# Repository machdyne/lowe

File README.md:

# Löwe FPGA Board

Löwe is an open-source FPGA development board for the Cologne Chip GateMate CCGM1A1.

This repo contains PCB layouts, schematics, pinouts and example gateware.

Find more information on the [Löwe product page](https://machdyne.com/product/lowe-fpga-board/).

## Examples

In order to build the examples, first edit rtl/config.mk and set the paths to the location of your toolchain. You can download the toolchain from [Cologne Chip](https://colognechip.com).

You can build each example with:

```
$ make && make impl
```

You can then use [openFPGALoader](https://github.com/trabucayre/openFPGALoader) to write the gateware to SRAM or flash, using a Raspberry Pi Pico or [Werkzeug](https://github.com/machdyne/werkzeug) (loaded with [pico-dirtyJtag](https://github.com/phdussud/pico-dirtyJtag)) in this example:

```
$ openFPGALoader -c dirtyJtag count_00.cfg.bit
```

## Configuration Mode Selection

The board has 4 DIP switches that select the configuration mode:

| Switches | Mode |
| -------- | ------ |
| 0000 | SPI Active Mode (CPOL=0 CPHA=0) |
| 0001 | SPI Active Mode (CPOL=0 CPHA=1) |
| 0010 | SPI Active Mode (CPOL=1 CPHA=0) |
| 0011 | SPI Active Mode (CPOL=1 CPHA=1) |
| 0100 | SPI Passive Mode (CPOL=0 CPHA=0) |
| 0101 | SPI Passive Mode (CPOL=0 CPHA=1) |
| 0110 | SPI Passive Mode (CPOL=1 CPHA=0) |
| 0111 | SPI Passive Mode (CPOL=1 CPHA=1) |
| 1100 | JTAG |

## MMOD Header

See the [MMOD repo](https://github.com/machdyne/mmod/) for details.

## JTAG Header

The 3.3V JTAG header can be used to program the FPGA SRAM as well as the MMOD flash memory.

```
5 3 1
6 4 2
```

| Pin | Signal |
| --- | ------ |
| 1 | TCK |
| 2 | TDI |
| 3 | TDO |
| 4 | TMS |
| 5 | 5V0[^1] |
| 6 | GND |

[^1]: This pin can be used to power the board with an external regulated 5V power supply, instead of USB power.

## Funding

This project was partially funded through the NGI0 Entrust Fund, a fund established by NLnet with financial support from the European Commission's Next Generation Internet programme.

## License

This project is released under the [CERN-OHL-P](LICENSE.txt) license.

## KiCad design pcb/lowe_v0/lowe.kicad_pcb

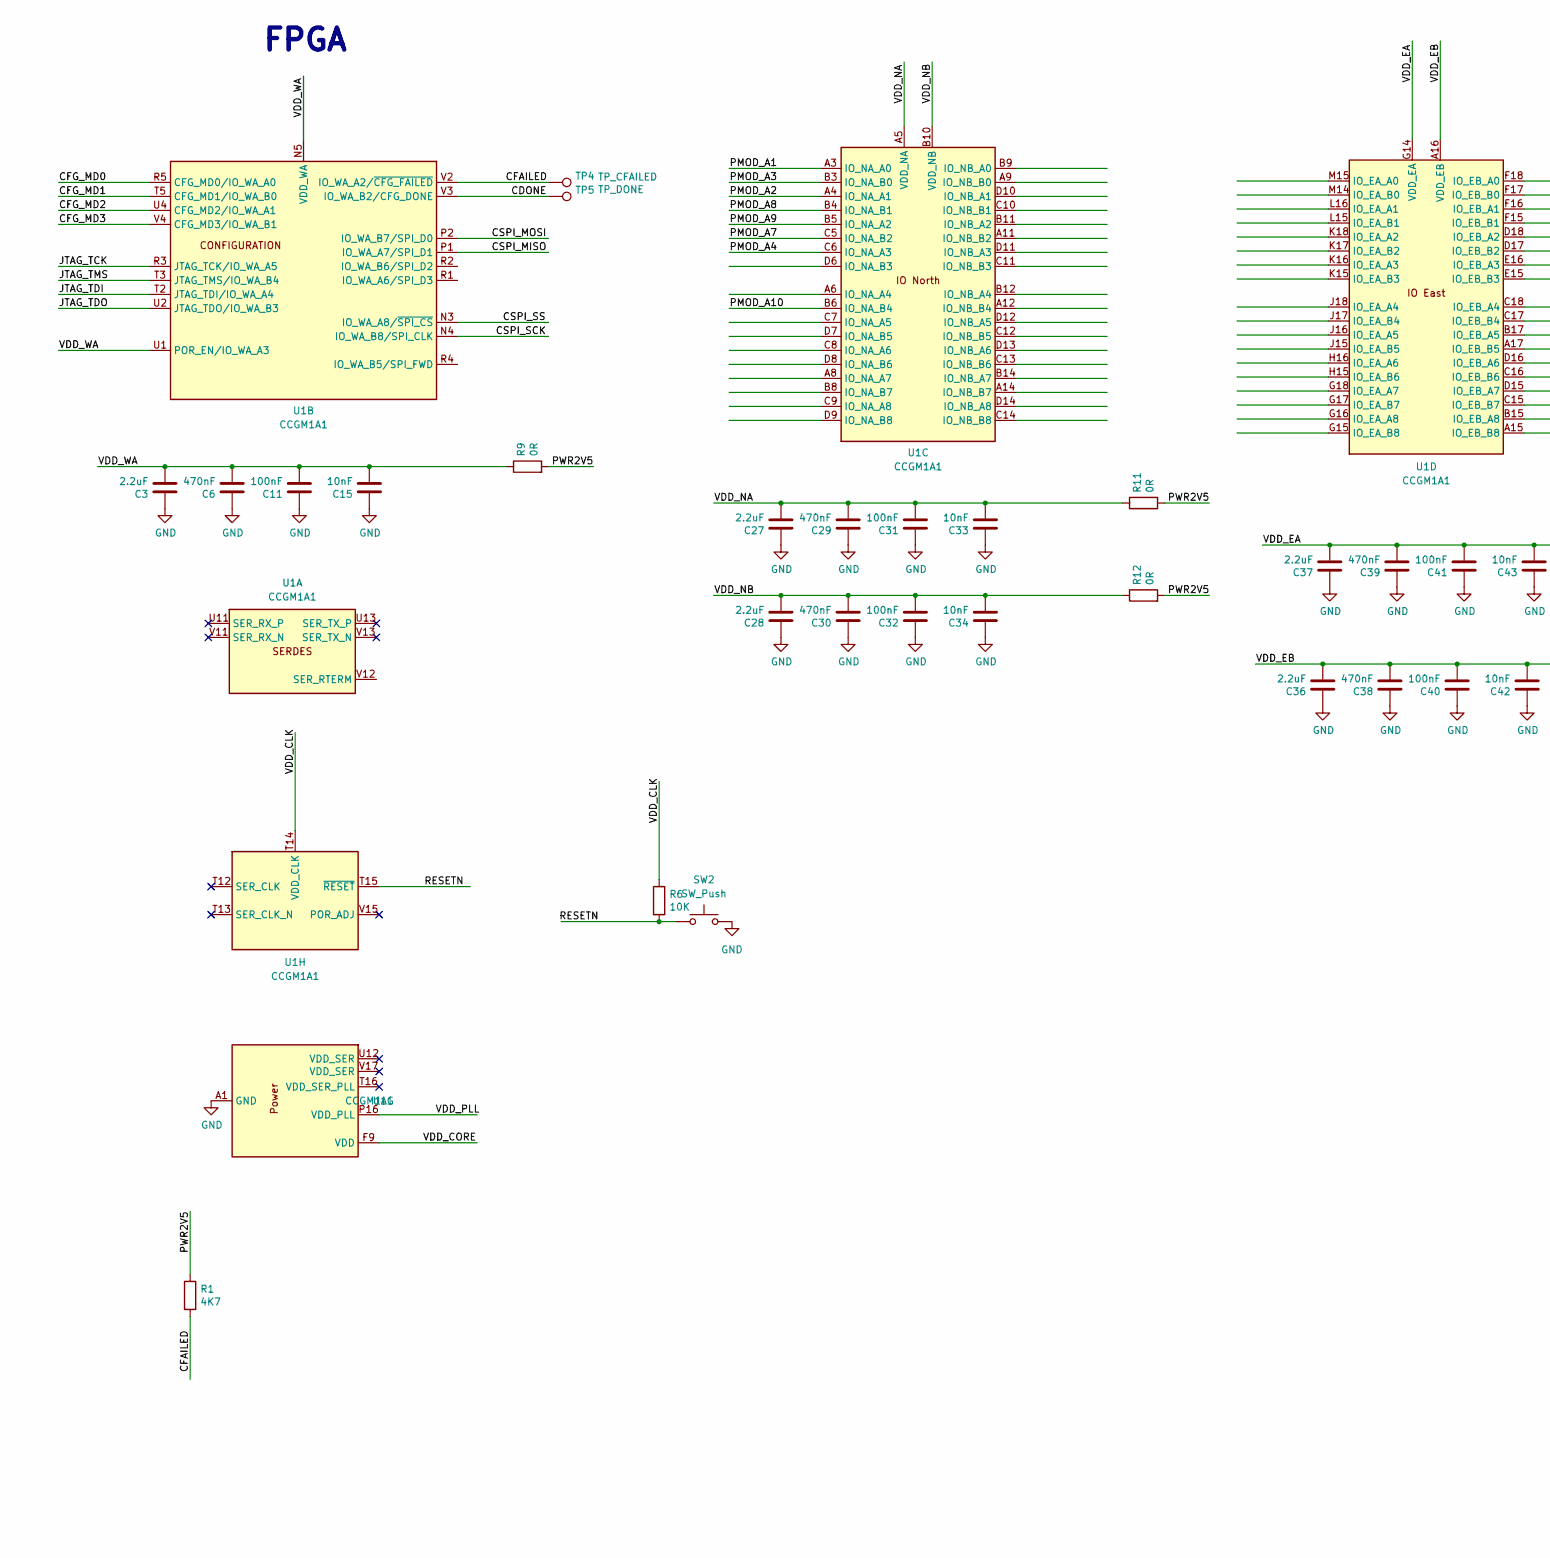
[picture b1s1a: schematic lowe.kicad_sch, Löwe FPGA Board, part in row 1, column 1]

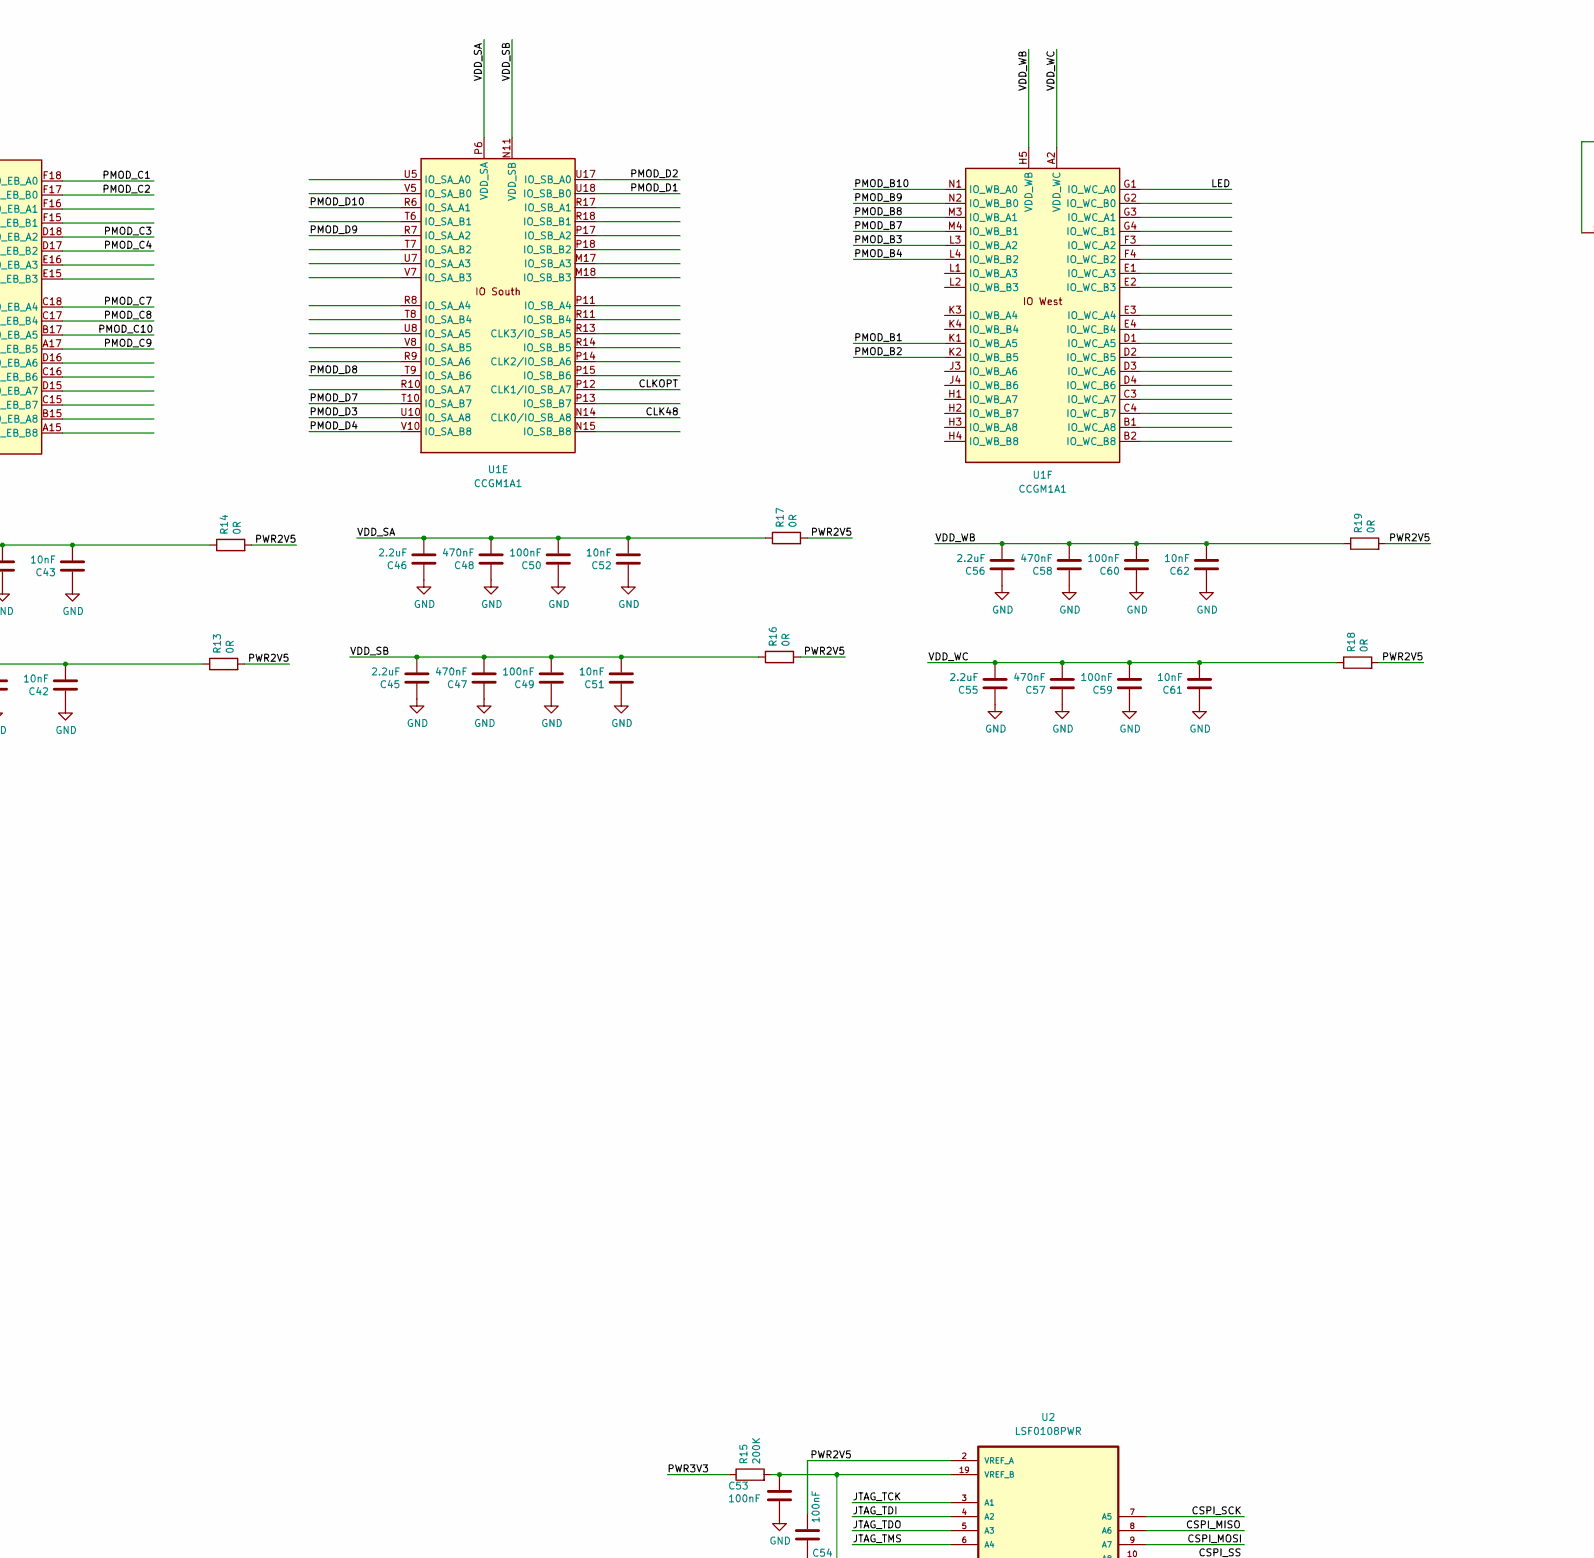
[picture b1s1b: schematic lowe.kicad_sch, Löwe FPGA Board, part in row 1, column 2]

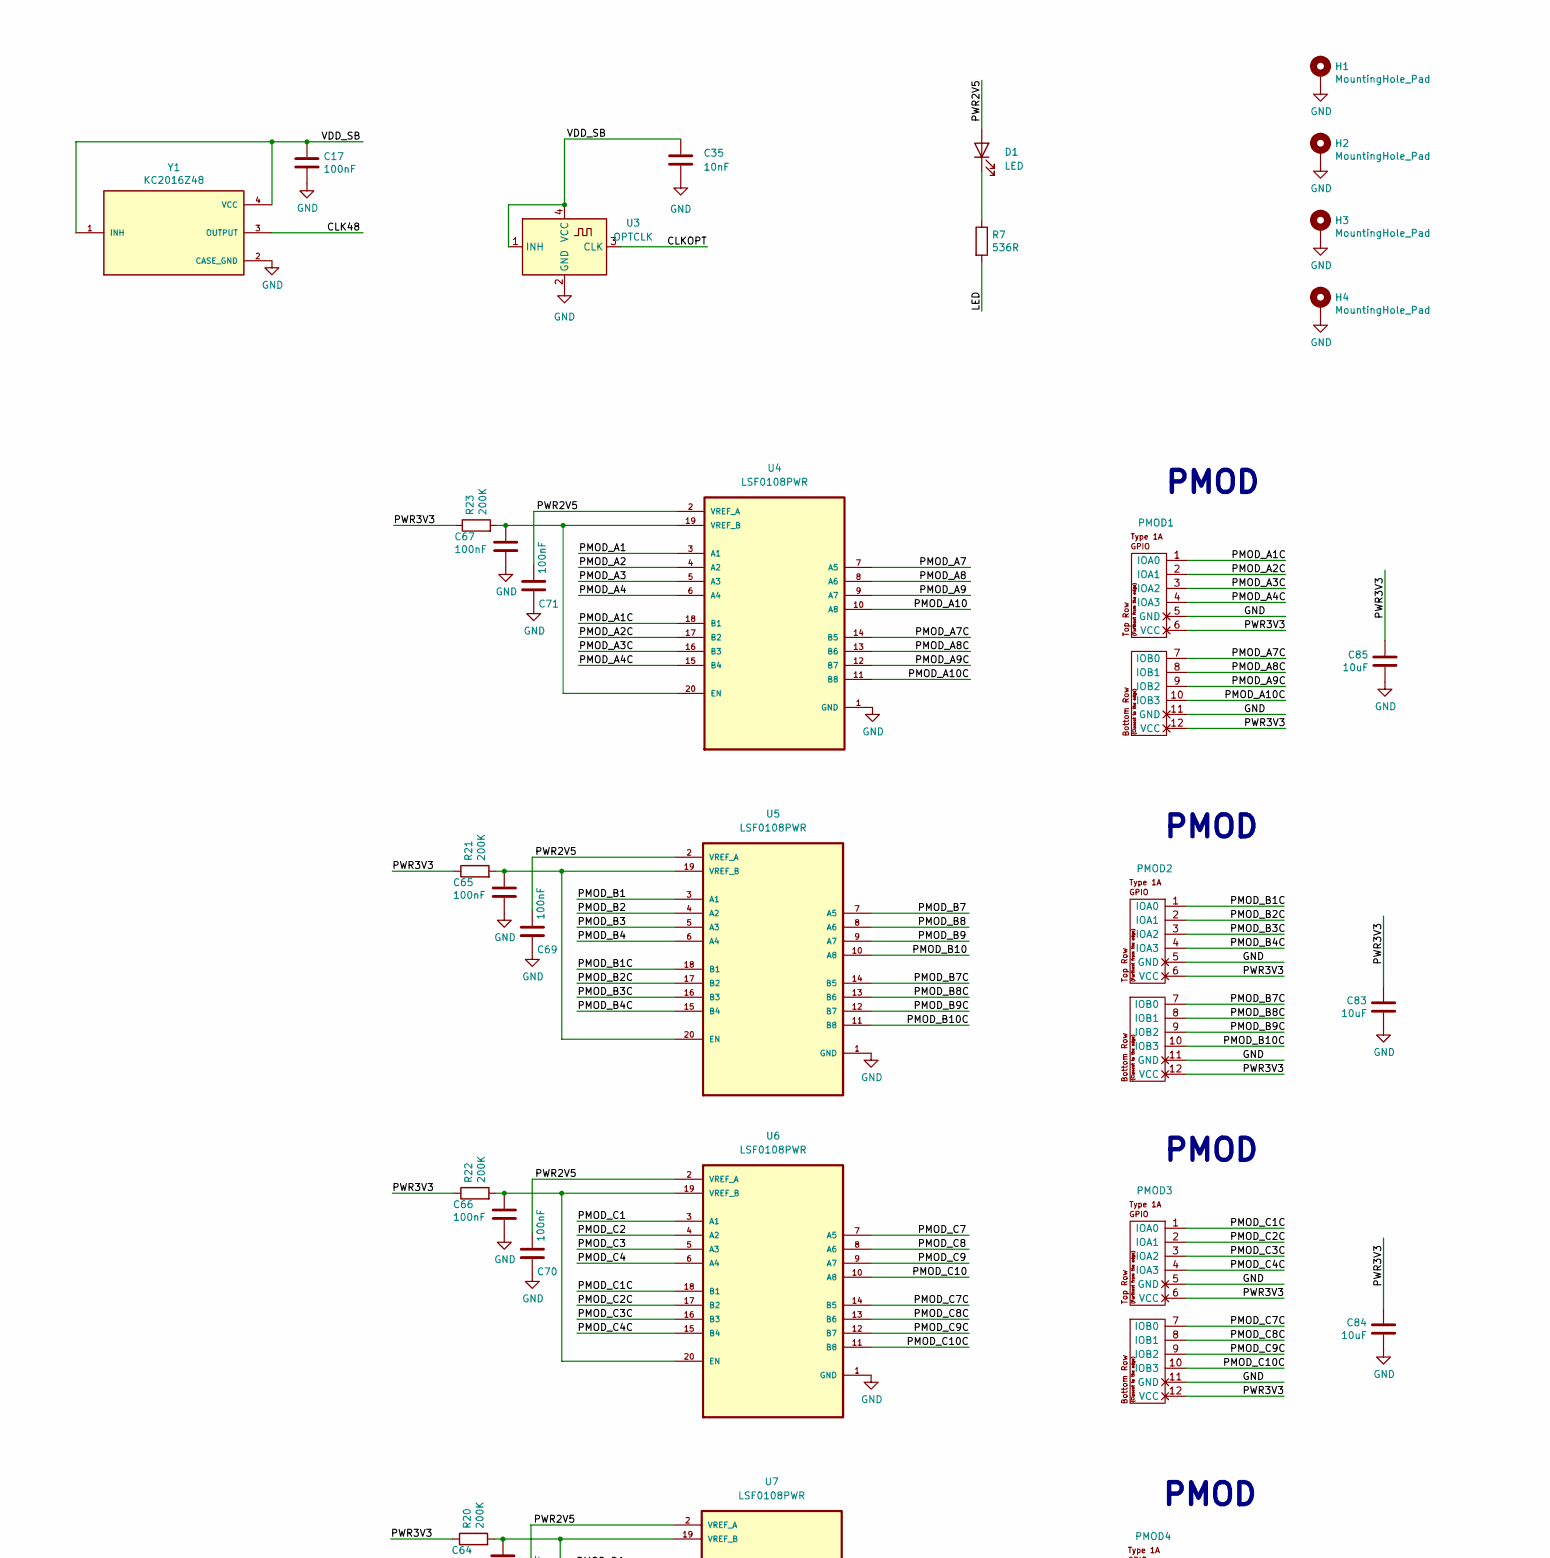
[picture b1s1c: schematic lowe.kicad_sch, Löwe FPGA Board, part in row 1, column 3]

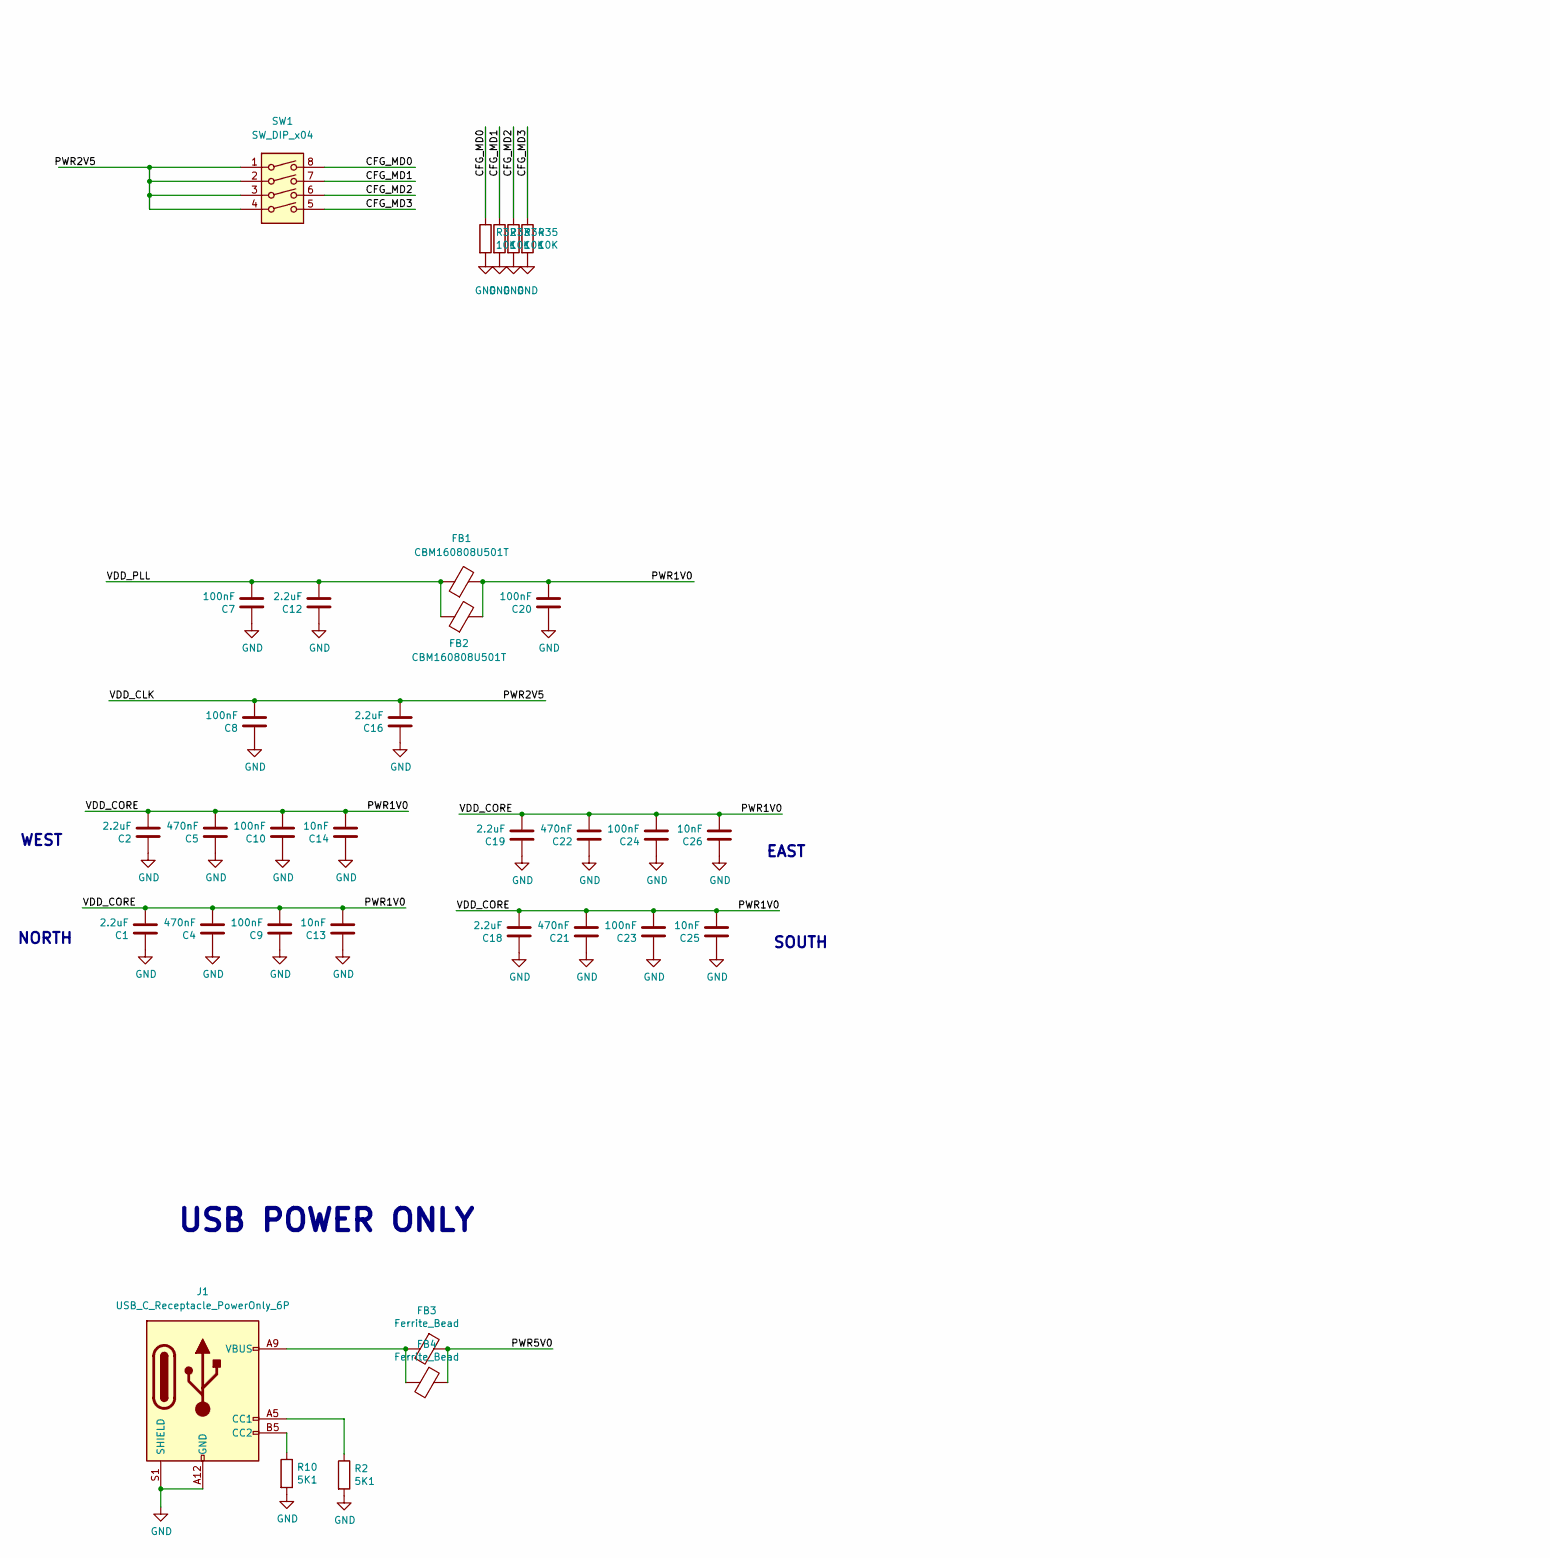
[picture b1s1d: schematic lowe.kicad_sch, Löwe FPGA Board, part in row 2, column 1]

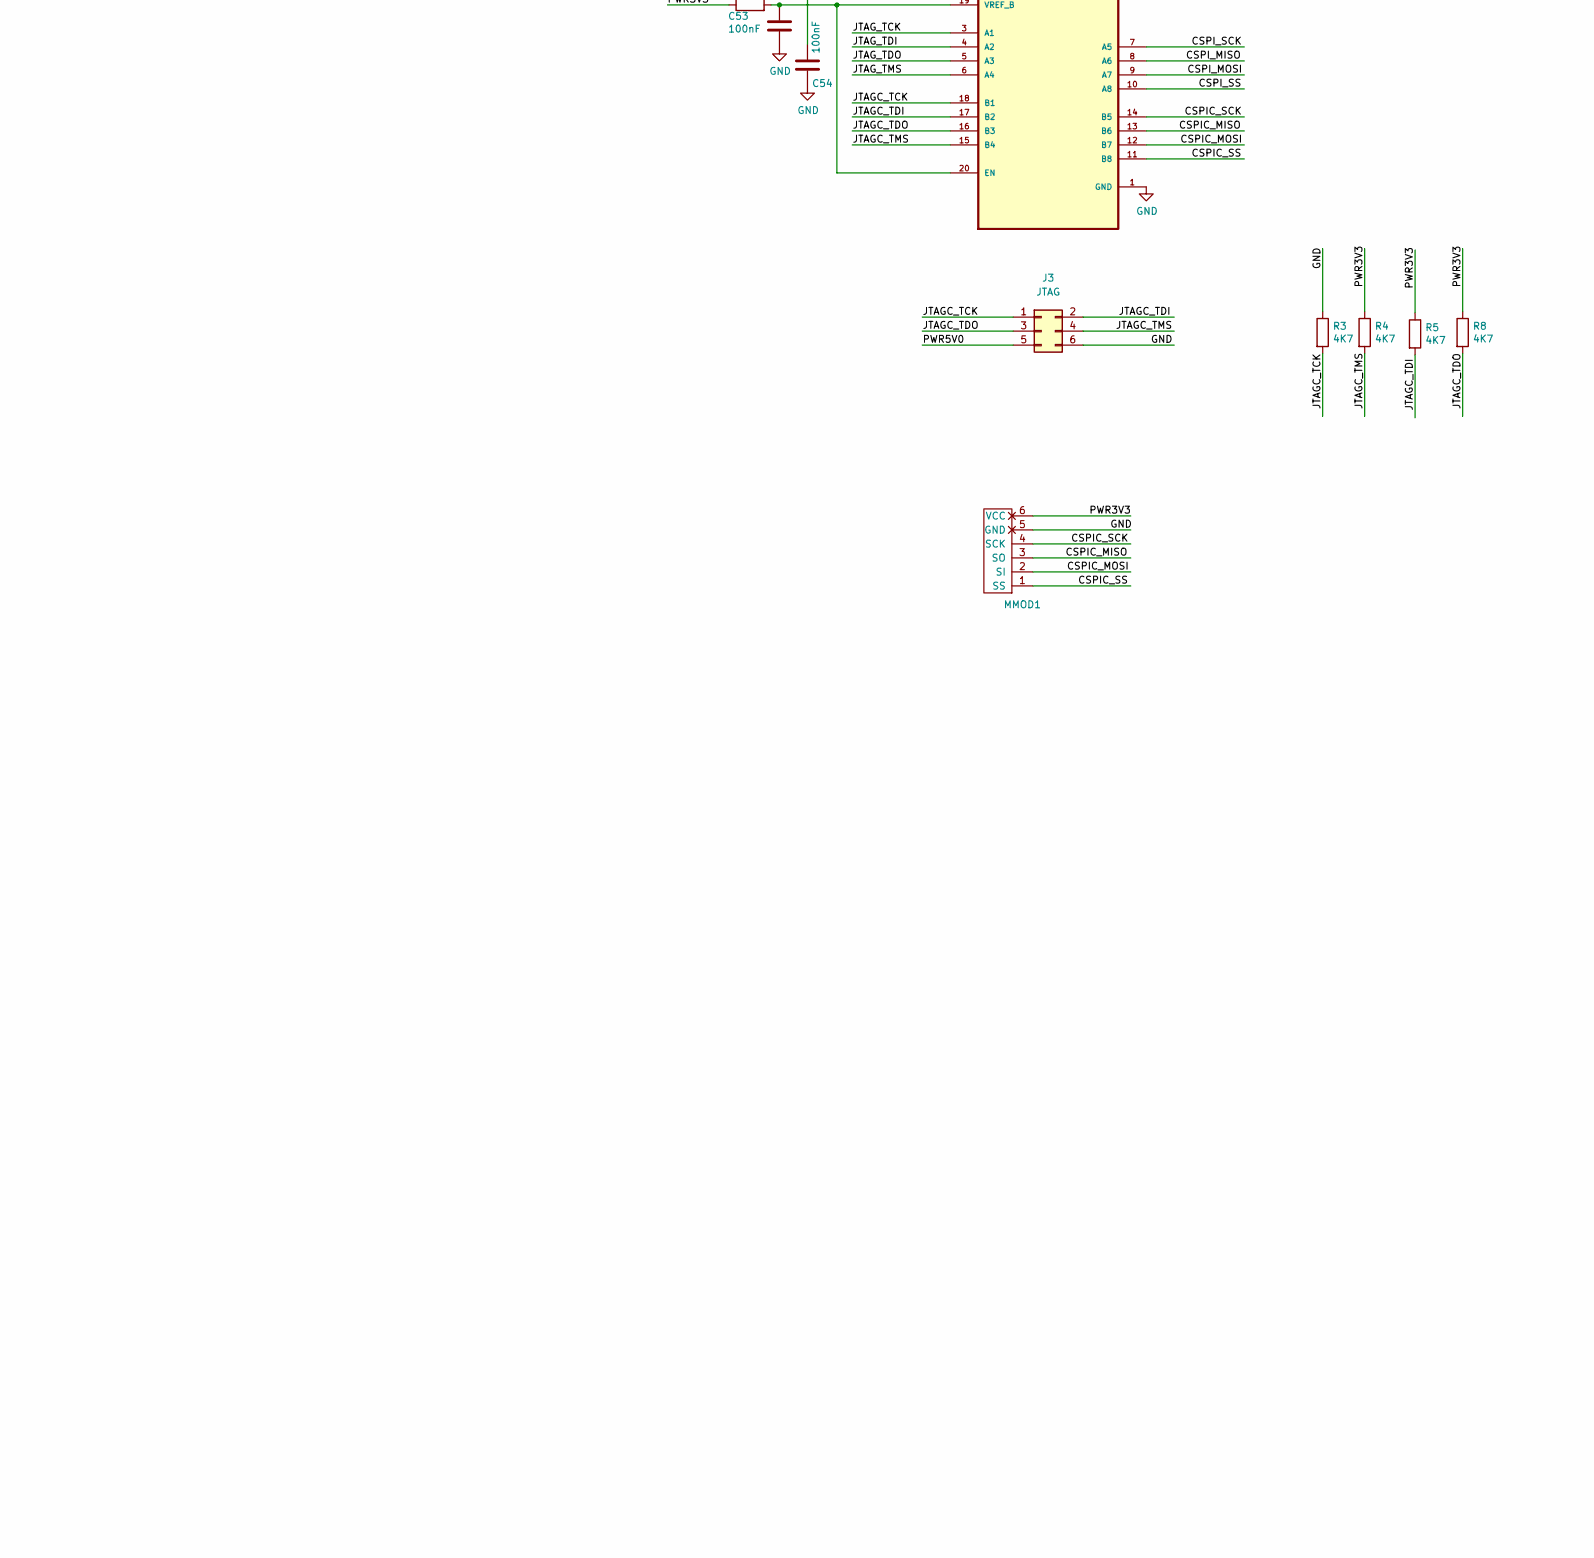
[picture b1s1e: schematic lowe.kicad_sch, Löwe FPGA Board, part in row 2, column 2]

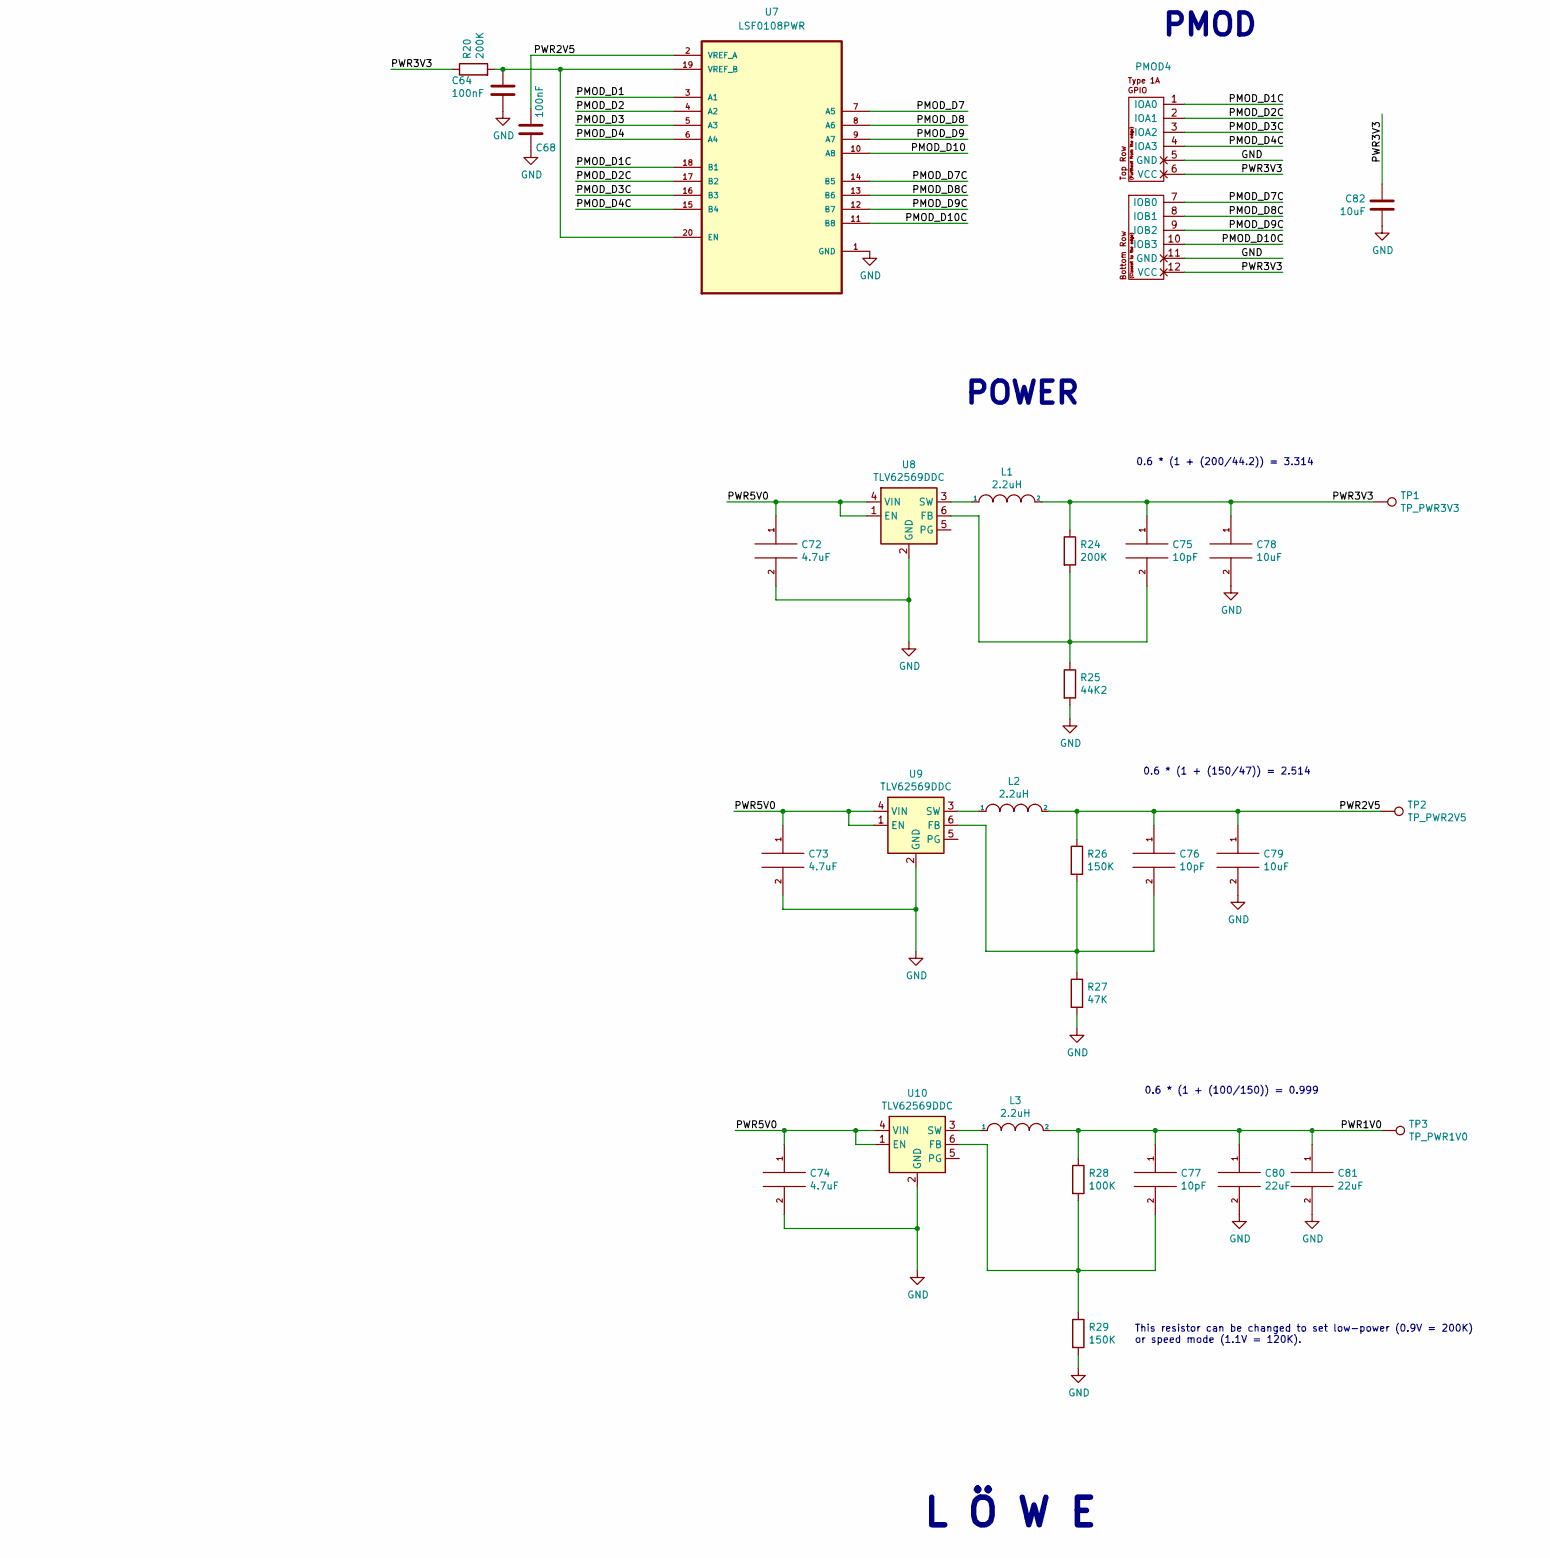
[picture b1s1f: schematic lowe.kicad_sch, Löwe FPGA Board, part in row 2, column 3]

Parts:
C1, C2, C3, C12, C16, C18, C19, C27, C28, C36, C37, C45, C46, C55, C56: 2.2uF; C_0603_1608Metric
C4, C5, C6, C21, C22, C29, C30, C38, C39, C47, C48, C57, C58: 470nF; C_0603_1608Metric
C7, C8, C9, C10, C11, C17, C20, C23, C24, C31, C32, C40, C41, C49, C50, C53, C54, C59, C60, C64, C65, C66, C67, C68, C69, C70, C71: 100nF; C_0603_1608Metric
C13, C14, C15, C25, C26, C33, C34, C35, C42, C43, C51, C52, C61, C62: 10nF; C_0603_1608Metric
C72, C73, C74: 4.7uF; C_0603_1608Metric
C75, C76, C77: 10pF; C_0603_1608Metric
C78, C79, C82, C83, C84, C85: 10uF; C_0603_1608Metric
C80, C81: 22uF; C_0603_1608Metric
D1: LED; LED_0603_1608Metric
FB1, FB2: CBM160808U501T; R_0603_1608Metric
FB3, FB4: Ferrite_Bead; R_0603_1608Metric
H1, H2, H3, H4: MountingHole_Pad; MountingHole_3.2mm_M3_Pad
J1: USB_C_Receptacle_PowerOnly_6P; GCT_USB4125-GF-A_REVA_BIGPADS
J3: JTAG; PinHeader_2x03_P2.54mm_Vertical
L1, L2, L3: 2.2uH; L_Taiyo-Yuden_MD-4040
MMOD1: PMOD-Device-x1-Type-2-SPI; MMOD_Host_Socket
PMOD1, PMOD2, PMOD3, PMOD4: PMOD-Device-x2-Type-1A-GPIO; PMOD_2x06_HOST
R1, R3, R4, R5, R8: 4K7; R_0603_1608Metric
R2, R10: 5K1; R_0603_1608Metric
R6, R32, R33, R34, R35: 10K; R_0603_1608Metric
R7: 536R; R_0603_1608Metric
R9, R11, R12, R13, R14, R16, R17, R18, R19: 0R; LD-NETTIE-0603
R15, R20, R21, R22, R23, R24: 200K; R_0603_1608Metric
R25: 44K2; R_0603_1608Metric
R26, R29: 150K; R_0603_1608Metric
R27: 47K; R_0603_1608Metric
R28: 100K; R_0603_1608Metric
SW1: SW_DIP_x04; SW_DIP_SPSTx04_Slide_6.7x11.72mm_W7.62mm_P2.54mm_LowProfile
SW2: SW_Push; Button_2P_3x4mm
TP1: TP_PWR3V3; TestPoint_THTPad_D1.0mm_Drill0.5mm
TP2: TP_PWR2V5; TestPoint_THTPad_D1.0mm_Drill0.5mm
TP3: TP_PWR1V0; TestPoint_THTPad_D1.0mm_Drill0.5mm
TP4: TP_CFAILED; TestPoint_Pad_1.0x1.0mm
TP5: TP_DONE; TestPoint_Pad_1.0x1.0mm
U1: CCGM1A1; BGA-324_15.0x15.0mm_Layout18x18_P0.8mm_Ball0.5mm_Pad0.4mm_N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
U2, U4, U5, U6, U7: LSF0108PWR; TSSOP-20_4.4x6.5mm_P0.65mm
U3: OPTCLK; Oscillator_SMD_Kyocera_KC2520Z-4Pin_2.5x2.0mm
U8, U9, U10: TLV62569DDC; SOT-23-6
Y1: KC2016Z48; OSC_KC2016Z13.5600C1KX00; PARTREV November 2020

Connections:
/CDONE: TP5.1, U1.V3 (IO_WA_B2/CFG_DONE)
/CFAILED: R1.2, TP4.1, U1.V2 (IO_WA_A2/~CFG_FAILED)
/CFG_MD0: R32.1, SW1.8, U1.R5 (CFG_MD0/IO_WA_A0)
/CFG_MD1: R33.1, SW1.7, U1.T5 (CFG_MD1/IO_WA_B0)
/CFG_MD2: R34.1, SW1.6, U1.U4 (CFG_MD2/IO_WA_A1)
/CFG_MD3: R35.1, SW1.5, U1.V4 (CFG_MD3/IO_WA_B1)
/CLK48: U1.N14 (CLK0/IO_SB_A8), Y1.3 (OUTPUT)
/CLKOPT: U1.P12 (CLK1/IO_SB_A7), U3.3 (CLK)
/CSPIC_MISO: MMOD1.3 (SO), U2.13 (B6)
/CSPIC_MOSI: MMOD1.2 (SI), U2.12 (B7)
/CSPIC_SCK: MMOD1.4 (SCK), U2.14 (B5)
/CSPIC_SS: MMOD1.1 (SS), U2.11 (B8)
/CSPI_MISO: U1.P1 (IO_WA_A7/SPI_D1), U2.8 (A6)
/CSPI_MOSI: U1.P2 (IO_WA_B7/SPI_D0), U2.9 (A7)
/CSPI_SCK: U1.N4 (IO_WA_B8/SPI_CLK), U2.7 (A5)
/CSPI_SS: U1.N3 (IO_WA_A8/~SPI_CS), U2.10 (A8)
/JTAGC_TCK: J3.1, R3.2, U2.18 (B1)
/JTAGC_TDI: J3.2, R5.2, U2.17 (B2)
/JTAGC_TDO: J3.3, R8.2, U2.16 (B3)
/JTAGC_TMS: J3.4, R4.2, U2.15 (B4)
/JTAG_TCK: U1.R3 (JTAG_TCK/IO_WA_A5), U2.3 (A1)
/JTAG_TDI: U1.T2 (JTAG_TDI/IO_WA_A4), U2.4 (A2)
/JTAG_TDO: U1.U2 (JTAG_TDO/IO_WA_B3), U2.5 (A3)
/JTAG_TMS: U1.T3 (JTAG_TMS/IO_WA_B4), U2.6 (A4)
/LED: R7.2, U1.G1 (IO_WC_A0)
/PMOD_A1: U1.A3 (IO_NA_A0), U4.3 (A1)
/PMOD_A1C: PMOD1.1 (IOA0), U4.18 (B1)
/PMOD_A2: U1.A4 (IO_NA_A1), U4.4 (A2)
/PMOD_A2C: PMOD1.2 (IOA1), U4.17 (B2)
/PMOD_A3: U1.B3 (IO_NA_B0), U4.5 (A3)
/PMOD_A3C: PMOD1.3 (IOA2), U4.16 (B3)
/PMOD_A4: U1.C6 (IO_NA_A3), U4.6 (A4)
/PMOD_A4C: PMOD1.4 (IOA3), U4.15 (B4)
/PMOD_A7: U1.C5 (IO_NA_B2), U4.7 (A5)
/PMOD_A7C: PMOD1.7 (IOB0), U4.14 (B5)
/PMOD_A8: U1.B4 (IO_NA_B1), U4.8 (A6)
/PMOD_A8C: PMOD1.8 (IOB1), U4.13 (B6)
/PMOD_A9: U1.B5 (IO_NA_A2), U4.9 (A7)
/PMOD_A9C: PMOD1.9 (IOB2), U4.12 (B7)
/PMOD_A10: U1.B6 (IO_NA_B4), U4.10 (A8)
/PMOD_A10C: PMOD1.10 (IOB3), U4.11 (B8)
/PMOD_B1: U1.K1 (IO_WB_A5), U5.3 (A1)
/PMOD_B1C: PMOD2.1 (IOA0), U5.18 (B1)
/PMOD_B2: U1.K2 (IO_WB_B5), U5.4 (A2)
/PMOD_B2C: PMOD2.2 (IOA1), U5.17 (B2)
/PMOD_B3: U1.L3 (IO_WB_A2), U5.5 (A3)
/PMOD_B3C: PMOD2.3 (IOA2), U5.16 (B3)
/PMOD_B4: U1.L4 (IO_WB_B2), U5.6 (A4)
/PMOD_B4C: PMOD2.4 (IOA3), U5.15 (B4)
/PMOD_B7: U1.M4 (IO_WB_B1), U5.7 (A5)
/PMOD_B7C: PMOD2.7 (IOB0), U5.14 (B5)
/PMOD_B8: U1.M3 (IO_WB_A1), U5.8 (A6)
/PMOD_B8C: PMOD2.8 (IOB1), U5.13 (B6)
/PMOD_B9: U1.N2 (IO_WB_B0), U5.9 (A7)
/PMOD_B9C: PMOD2.9 (IOB2), U5.12 (B7)
/PMOD_B10: U1.N1 (IO_WB_A0), U5.10 (A8)
/PMOD_B10C: PMOD2.10 (IOB3), U5.11 (B8)
/PMOD_C1: U1.F18 (IO_EB_A0), U6.3 (A1)
/PMOD_C1C: PMOD3.1 (IOA0), U6.18 (B1)
/PMOD_C2: U1.F17 (IO_EB_B0), U6.4 (A2)
/PMOD_C2C: PMOD3.2 (IOA1), U6.17 (B2)
/PMOD_C3: U1.D18 (IO_EB_A2), U6.5 (A3)
/PMOD_C3C: PMOD3.3 (IOA2), U6.16 (B3)
/PMOD_C4: U1.D17 (IO_EB_B2), U6.6 (A4)
/PMOD_C4C: PMOD3.4 (IOA3), U6.15 (B4)
/PMOD_C7: U1.C18 (IO_EB_A4), U6.7 (A5)
/PMOD_C7C: PMOD3.7 (IOB0), U6.14 (B5)
/PMOD_C8: U1.C17 (IO_EB_B4), U6.8 (A6)
/PMOD_C8C: PMOD3.8 (IOB1), U6.13 (B6)
/PMOD_C9: U1.A17 (IO_EB_B5), U6.9 (A7)
/PMOD_C9C: PMOD3.9 (IOB2), U6.12 (B7)
/PMOD_C10: U1.B17 (IO_EB_A5), U6.10 (A8)
/PMOD_C10C: PMOD3.10 (IOB3), U6.11 (B8)
/PMOD_D1: U1.U18 (IO_SB_B0), U7.3 (A1)
/PMOD_D1C: PMOD4.1 (IOA0), U7.18 (B1)
/PMOD_D2: U1.U17 (IO_SB_A0), U7.4 (A2)
/PMOD_D2C: PMOD4.2 (IOA1), U7.17 (B2)
/PMOD_D3: U1.U10 (IO_SA_A8), U7.5 (A3)
/PMOD_D3C: PMOD4.3 (IOA2), U7.16 (B3)
/PMOD_D4: U1.V10 (IO_SA_B8), U7.6 (A4)
/PMOD_D4C: PMOD4.4 (IOA3), U7.15 (B4)
/PMOD_D7: U1.T10 (IO_SA_B7), U7.7 (A5)
/PMOD_D7C: PMOD4.7 (IOB0), U7.14 (B5)
/PMOD_D8: U1.T9 (IO_SA_B6), U7.8 (A6)
/PMOD_D8C: PMOD4.8 (IOB1), U7.13 (B6)
/PMOD_D9: U1.R7 (IO_SA_A2), U7.9 (A7)
/PMOD_D9C: PMOD4.9 (IOB2), U7.12 (B7)
/PMOD_D10: U1.R6 (IO_SA_A1), U7.10 (A8)
/PMOD_D10C: PMOD4.10 (IOB3), U7.11 (B8)
/PWR1V0: C1.2, C2.2, C4.2, C5.2, C9.2, C10.2, C13.2, C14.2, C18.2, C19.2, C20.2, C21.2, C22.2, C23.2, C24.2, C25.2, C26.2, C77.1, C80.1, C81.1, FB1.2, FB2.2, L3.2, R28.1, TP3.1, U1.F9 (VDD), U1.G6 (VDD), U1.G8 (VDD), U1.G10 (VDD), U1.G12 (VDD), U1.H7 (VDD), U1.H9 (VDD), U1.H11 (VDD), U1.H13 (VDD), U1.J6 (VDD), U1.J8 (VDD), U1.J10 (VDD), U1.J12 (VDD), U1.K7 (VDD), U1.K9 (VDD), U1.K11 (VDD), U1.K13 (VDD), U1.L6 (VDD), U1.L8 (VDD), U1.L10 (VDD), U1.L12 (VDD), U1.M7 (VDD), U1.M9 (VDD), U1.M11 (VDD), U1.M13 (VDD), U1.N6 (VDD), U1.N8 (VDD), U1.N10 (VDD)
/PWR2V5: C8.2, C16.2, C54.1, C68.1, C69.1, C70.1, C71.1, C76.1, C79.1, D1.2 (A), L2.2, R1.1, R6.1, R9.2, R11.2, R12.2, R13.2, R14.2, R16.2, R17.2, R18.2, R19.2, R26.1, SW1.1, SW1.2, SW1.3, SW1.4, TP2.1, U1.T14 (VDD_CLK), U2.2 (VREF_A), U4.2 (VREF_A), U5.2 (VREF_A), U6.2 (VREF_A), U7.2 (VREF_A)
/PWR3V3: C75.1, C78.1, C82.1, C83.1, C84.1, C85.1, L1.2, MMOD1.6 (VCC), PMOD1.6 (VCC), PMOD1.12 (VCC), PMOD2.6 (VCC), PMOD2.12 (VCC), PMOD3.6 (VCC), PMOD3.12 (VCC), PMOD4.6 (VCC), PMOD4.12 (VCC), R4.1, R5.1, R8.1, R15.1, R20.1, R21.1, R22.1, R23.1, R24.1, TP1.1
/PWR5V0: C72.1, C73.1, C74.1, FB3.1, FB4.1, J3.5, U8.1 (EN), U8.4 (VIN), U9.1 (EN), U9.4 (VIN), U10.1 (EN), U10.4 (VIN)
/RESETN: R6.2, SW2.1, U1.T15 (~RESET)
/VDD_EA: C37.2, C39.2, C41.2, C43.2, R14.1, U1.G14 (VDD_EA), U1.H17 (VDD_EA), U1.J14 (VDD_EA), U1.L14 (VDD_EA), U1.L17 (VDD_EA)
/VDD_EB: C36.2, C38.2, C40.2, C42.2, R13.1, U1.A16 (VDD_EB), U1.B18 (VDD_EB), U1.E14 (VDD_EB), U1.E17 (VDD_EB), U1.F13 (VDD_EB)
/VDD_NA: C27.2, C29.2, C31.2, C33.2, R11.1, U1.A5 (VDD_NA), U1.B7 (VDD_NA), U1.E6 (VDD_NA), U1.E8 (VDD_NA), U1.F7 (VDD_NA)
/VDD_NB: C28.2, C30.2, C32.2, C34.2, R12.1, U1.B10 (VDD_NB), U1.B13 (VDD_NB), U1.E10 (VDD_NB), U1.E12 (VDD_NB), U1.F11 (VDD_NB)
/VDD_PLL: C7.2, C12.2, FB1.1, FB2.1, U1.P16 (VDD_PLL)
/VDD_SA: C46.2, C48.2, C50.2, C52.2, R17.1, U1.P6 (VDD_SA), U1.P8 (VDD_SA), U1.P10 (VDD_SA), U1.U6 (VDD_SA), U1.U9 (VDD_SA)
/VDD_SB: C17.1, C35.1, C45.2, C47.2, C49.2, C51.2, R16.1, U1.N11 (VDD_SB), U1.N13 (VDD_SB), U1.N18 (VDD_SB), U1.R15 (VDD_SB), U1.T18 (VDD_SB), U3.1 (INH), U3.4 (VCC), Y1.1 (INH), Y1.4 (VCC)
/VDD_WA: C3.2, C6.2, C11.2, C15.2, R9.1, U1.N5 (VDD_WA), U1.P3 (VDD_WA), U1.P5 (VDD_WA), U1.T1 (VDD_WA), U1.U1 (POR_EN/IO_WA_A3), U1.U3 (VDD_WA)
/VDD_WB: C56.2, C58.2, C60.2, C62.2, R19.1, U1.H5 (VDD_WB), U1.J2 (VDD_WB), U1.K5 (VDD_WB), U1.M2 (VDD_WB), U1.M5 (VDD_WB)
/VDD_WC: C55.2, C57.2, C59.2, C61.2, R18.1, U1.A2 (VDD_WC), U1.C2 (VDD_WC), U1.D5 (VDD_WC), U1.F2 (VDD_WC), U1.F5 (VDD_WC)
GND: C1.1, C2.1, C3.1, C4.1, C5.1, C6.1, C7.1, C8.1, C9.1, C10.1, C11.1, C12.1, C13.1, C14.1, C15.1, C16.1, C17.2, C18.1, C19.1, C20.1, C21.1, C22.1, C23.1, C24.1, C25.1, C26.1, C27.1, C28.1, C29.1, C30.1, C31.1, C32.1, C33.1, C34.1, C35.2, C36.1, C37.1, C38.1, C39.1, C40.1, C41.1, C42.1, C43.1, C45.1, C46.1, C47.1, C48.1, C49.1, C50.1, C51.1, C52.1, C53.2, C54.2, C55.1, C56.1, C57.1, C58.1, C59.1, C60.1, C61.1, C62.1, C64.2, C65.2, C66.2, C67.2, C68.2, C69.2, C70.2, C71.2, C72.2, C73.2, C74.2, C78.2, C79.2, C80.2, C81.2, C82.2, C83.2, C84.2, C85.2, H1.1, H2.1, H3.1, H4.1, J1.A12 (GND), J1.B12 (GND), J1.S1 (SHIELD), J3.6, MMOD1.5 (GND), PMOD1.5 (GND), PMOD1.11 (GND), PMOD2.5 (GND), PMOD2.11 (GND), PMOD3.5 (GND), PMOD3.11 (GND), PMOD4.5 (GND), PMOD4.11 (GND), R2.2, R3.1, R10.2, R25.2, R27.2, R29.2, R32.2, R33.2, R34.2, R35.2, SW2.2, U1.A1 (GND), U1.A7 (GND), U1.A10 (GND), U1.A13 (GND), U1.A18 (GND), U1.B16 (GND), U1.C1 (GND), U1.E5 (GND), U1.E7 (GND), U1.E9 (GND), U1.E11 (GND), U1.E13 (GND), U1.E18 (GND), U1.F1 (GND), U1.F6 (GND), U1.F8 (GND), U1.F10 (GND), U1.F12 (GND), U1.F14 (GND), U1.G5 (GND), U1.G7 (GND), U1.G9 (GND), U1.G11 (GND), U1.G13 (GND), U1.H6 (GND), U1.H8 (GND), U1.H10 (GND), U1.H12 (GND), U1.H14 (GND), U1.H18 (GND), U1.J1 (GND), U1.J5 (GND), U1.J7 (GND), U1.J9 (GND), U1.J11 (GND), U1.J13 (GND), U1.K6 (GND), U1.K8 (GND), U1.K10 (GND), U1.K12 (GND), U1.K14 (GND), U1.L5 (GND), U1.L7 (GND), U1.L9 (GND), U1.L11 (GND), U1.L13 (GND), U1.L18 (GND), U1.M1 (GND), U1.M6 (GND), U1.M8 (GND), U1.M10 (GND), U1.M12 (GND), U1.M16 (GND), U1.N7 (GND), U1.N9 (GND), U1.N12 (GND), U1.N17 (GND), U1.P4 (GND), U1.P7 (GND), U1.P9 (GND), U1.R12 (GND), U1.R16 (GND), U1.T4 (GND), U1.T11 (GND), U1.T17 (GND), U1.U14 (GND), U1.U15 (GND), U1.U16 (GND), U1.V1 (GND), U1.V6 (GND), U1.V9 (GND), U1.V14 (GND), U1.V16 (GND), U1.V18 (GND), U2.1 (GND), U3.2 (GND), U4.1 (GND), U5.1 (GND), U6.1 (GND), U7.1 (GND), U8.2 (GND), U9.2 (GND), U10.2 (GND), Y1.2 (CASE_GND)
unnamed: C53.1, R15.2, U2.19 (VREF_B), U2.20 (EN)
unnamed: C64.1, R20.2, U7.19 (VREF_B), U7.20 (EN)
unnamed: C65.1, R21.2, U5.19 (VREF_B), U5.20 (EN)
unnamed: C66.1, R22.2, U6.19 (VREF_B), U6.20 (EN)
unnamed: C67.1, R23.2, U4.19 (VREF_B), U4.20 (EN)
unnamed: C75.2, R24.2, R25.1, U8.6 (FB)
unnamed: C76.2, R26.2, R27.1, U9.6 (FB)
unnamed: C77.2, R28.2, R29.1, U10.6 (FB)
unnamed: D1.1 (K), R7.1
unnamed: FB3.2, FB4.2, J1.A9 (VBUS), J1.B9 (VBUS)
unnamed: J1.A5 (CC1), R2.1
unnamed: J1.B5 (CC2), R10.1
unnamed: L1.1, U8.3 (SW)
unnamed: L2.1, U9.3 (SW)
unnamed: L3.1, U10.3 (SW)

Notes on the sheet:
EAST
This resistor can be changed to set low-power (0.9V = 200K) or speed mode (1.1V = 120K).
WEST
PMOD
FPGA
0.6 * (1 + (150/47)) = 2.514
NORTH
L Ö W E
0.6 * (1 + (100/150)) = 0.999
POWER
0.6 * (1 + (200/44.2)) = 3.314
USB POWER ONLY
SOUTH

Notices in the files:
pcb/lowe_v0/lowe.kicad_sch:
Copyright © 2023 Lone Dynamics Corporation
